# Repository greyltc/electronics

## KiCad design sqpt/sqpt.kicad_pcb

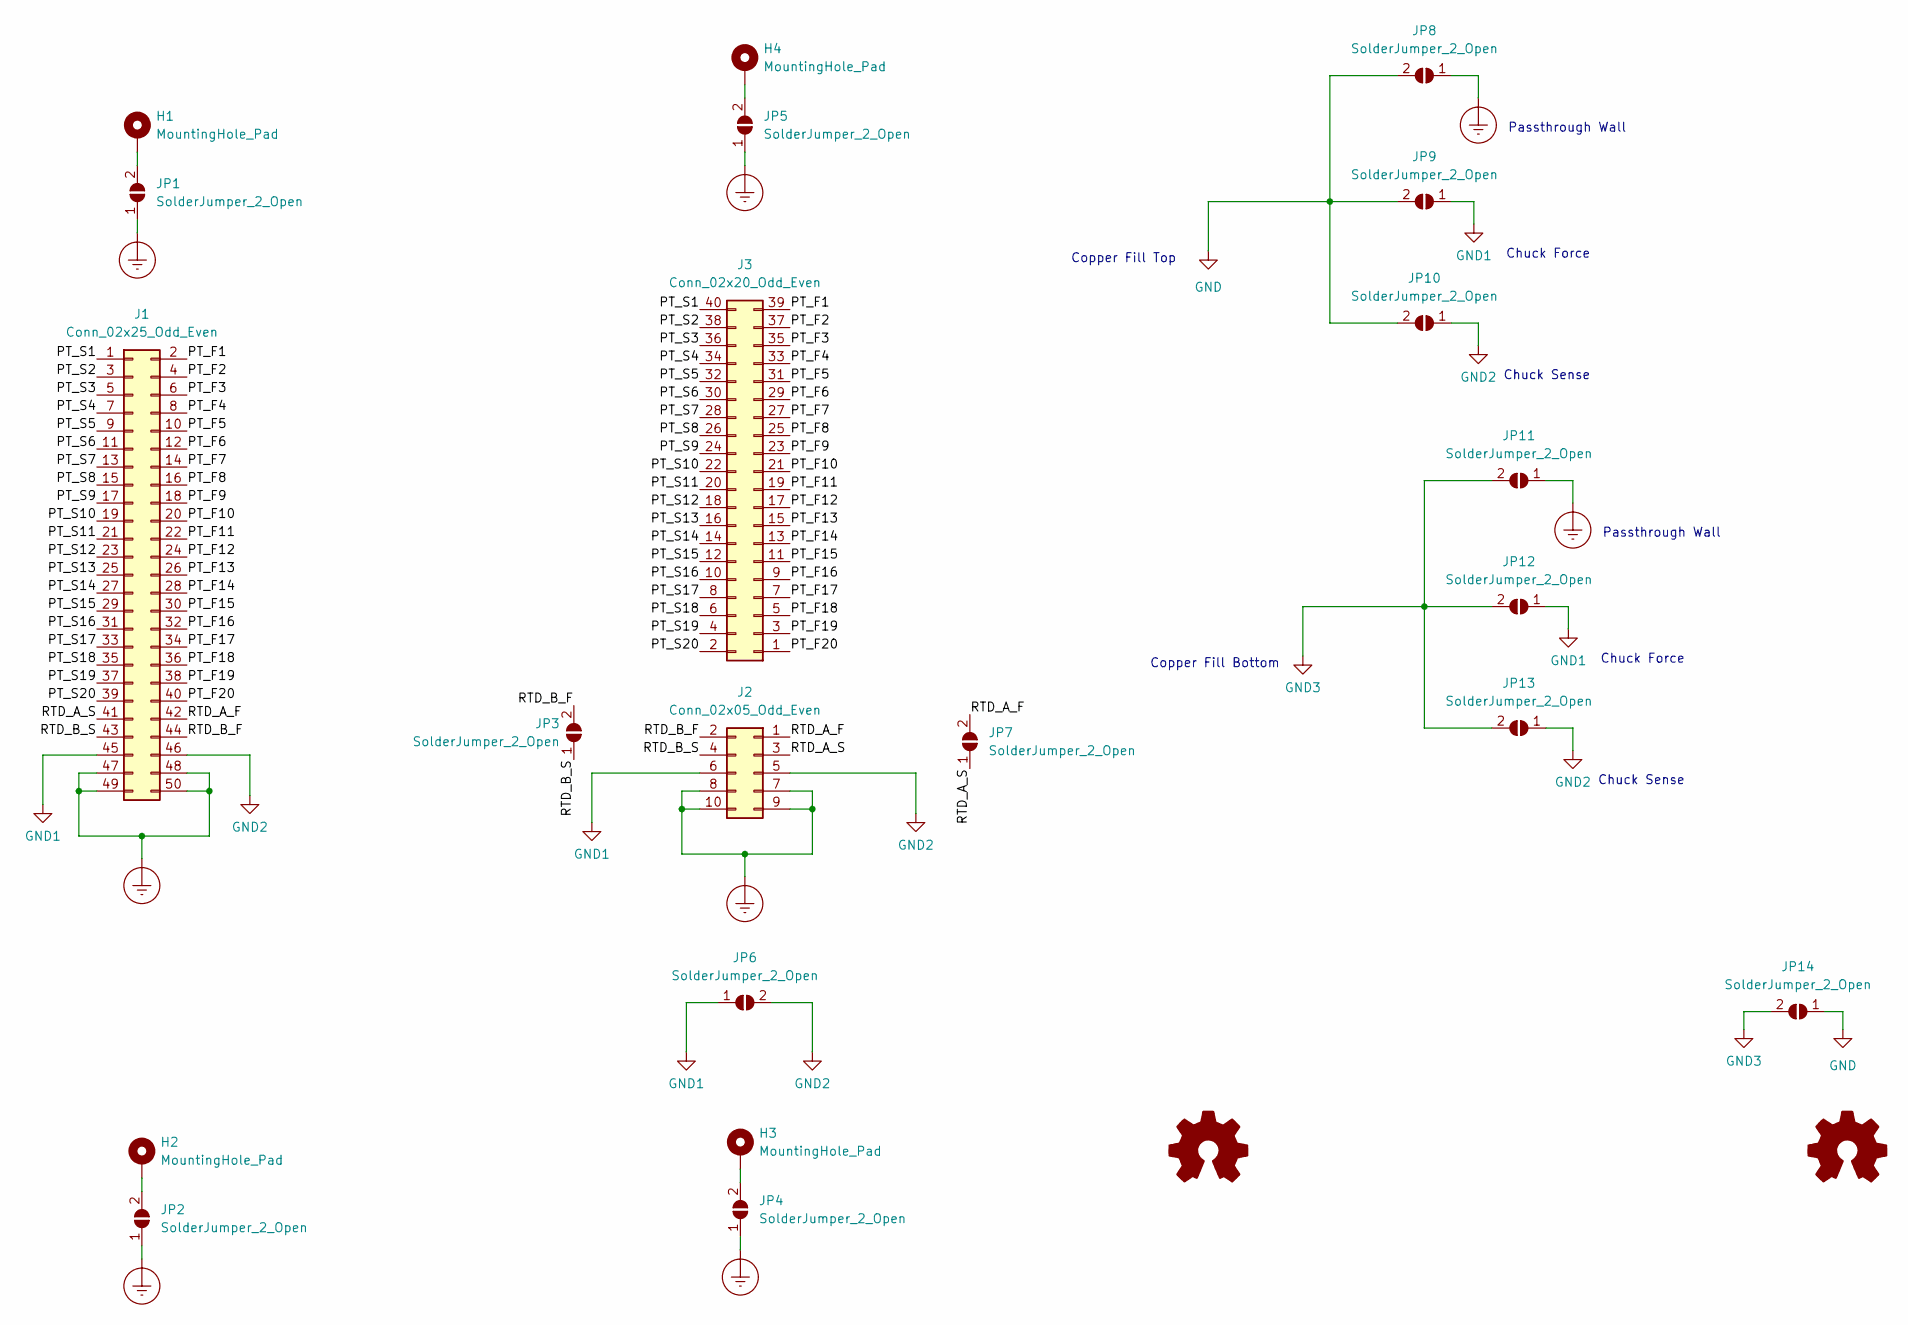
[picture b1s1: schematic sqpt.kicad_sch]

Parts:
H1, H2, H3, H4: MountingHole_Pad; MountingHole_3.2mm_M3_ISO14580_Pad
J1: Conn_02x25_Odd_Even; TST-125-01-G-D
J2: Conn_02x05_Odd_Even; PinHeader_2x05_P2.54mm_Vertical
J3: Conn_02x20_Odd_Even; TST-120-01-G-D
JP1, JP2, JP3, JP4, JP5, JP6, JP7, JP8, JP9, JP10, JP11, JP12, JP13, JP14: SolderJumper_2_Open; SolderJumper-2_P1.3mm_Open_RoundedPad1.0x1.5mm
LOGO1, LOGO2: Logo_Open_Hardware_Small; site_small

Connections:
/PT_F1: J1.2, J3.39
/PT_F2: J1.4, J3.37
/PT_F3: J1.6, J3.35
/PT_F4: J1.8, J3.33
/PT_F5: J1.10, J3.31
/PT_F6: J1.12, J3.29
/PT_F7: J1.14, J3.27
/PT_F8: J1.16, J3.25
/PT_F9: J1.18, J3.23
/PT_F10: J1.20, J3.21
/PT_F11: J1.22, J3.19
/PT_F12: J1.24, J3.17
/PT_F13: J1.26, J3.15
/PT_F14: J1.28, J3.13
/PT_F15: J1.30, J3.11
/PT_F16: J1.32, J3.9
/PT_F17: J1.34, J3.7
/PT_F18: J1.36, J3.5
/PT_F19: J1.38, J3.3
/PT_F20: J1.40, J3.1
/PT_S1: J1.1, J3.40
/PT_S2: J1.3, J3.38
/PT_S3: J1.5, J3.36
/PT_S4: J1.7, J3.34
/PT_S5: J1.9, J3.32
/PT_S6: J1.11, J3.30
/PT_S7: J1.13, J3.28
/PT_S8: J1.15, J3.26
/PT_S9: J1.17, J3.24
/PT_S10: J1.19, J3.22
/PT_S11: J1.21, J3.20
/PT_S12: J1.23, J3.18
/PT_S13: J1.25, J3.16
/PT_S14: J1.27, J3.14
/PT_S15: J1.29, J3.12
/PT_S16: J1.31, J3.10
/PT_S17: J1.33, J3.8
/PT_S18: J1.35, J3.6
/PT_S19: J1.37, J3.4
/PT_S20: J1.39, J3.2
/RTD_A_F: J1.42, J2.1, JP7.2 (B)
/RTD_A_S: J1.41, J2.3, JP7.1 (A)
/RTD_B_F: J1.44, J2.2, JP3.2 (B)
/RTD_B_S: J1.43, J2.4, JP3.1 (A)
Earth_Protective: J1.47, J1.48, J1.49, J1.50, J2.7, J2.8, J2.9, J2.10, JP1.1 (A), JP2.1 (A), JP4.1 (A), JP5.1 (A), JP8.1 (A), JP11.1 (A)
GND: JP8.2 (B), JP9.2 (B), JP10.2 (B), JP14.1 (A)
GND1: J1.45, J2.6, JP6.1 (A), JP9.1 (A), JP12.1 (A)
GND2: J1.46, J2.5, JP6.2 (B), JP10.1 (A), JP13.1 (A)
GND3: JP11.2 (B), JP12.2 (B), JP13.2 (B), JP14.2 (B)
unnamed: H1.1, JP1.2 (B)
unnamed: H2.1, JP2.2 (B)
unnamed: H3.1, JP4.2 (B)
unnamed: H4.1, JP5.2 (B)

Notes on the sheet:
Chuck Force
Passthrough Wall
Copper Fill Bottom
Chuck Sense
Copper Fill Top

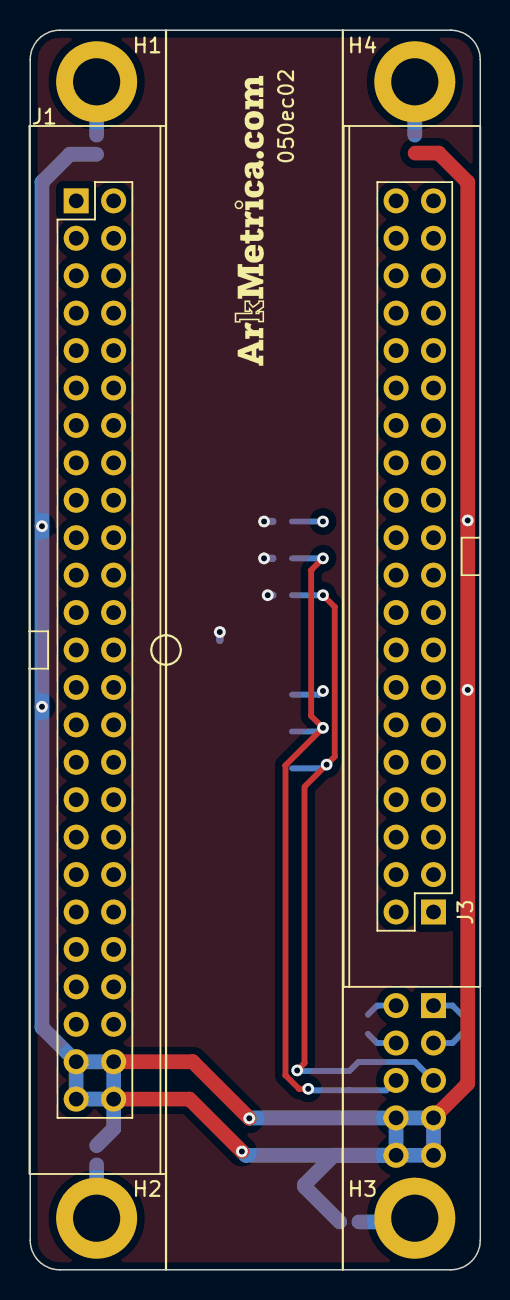
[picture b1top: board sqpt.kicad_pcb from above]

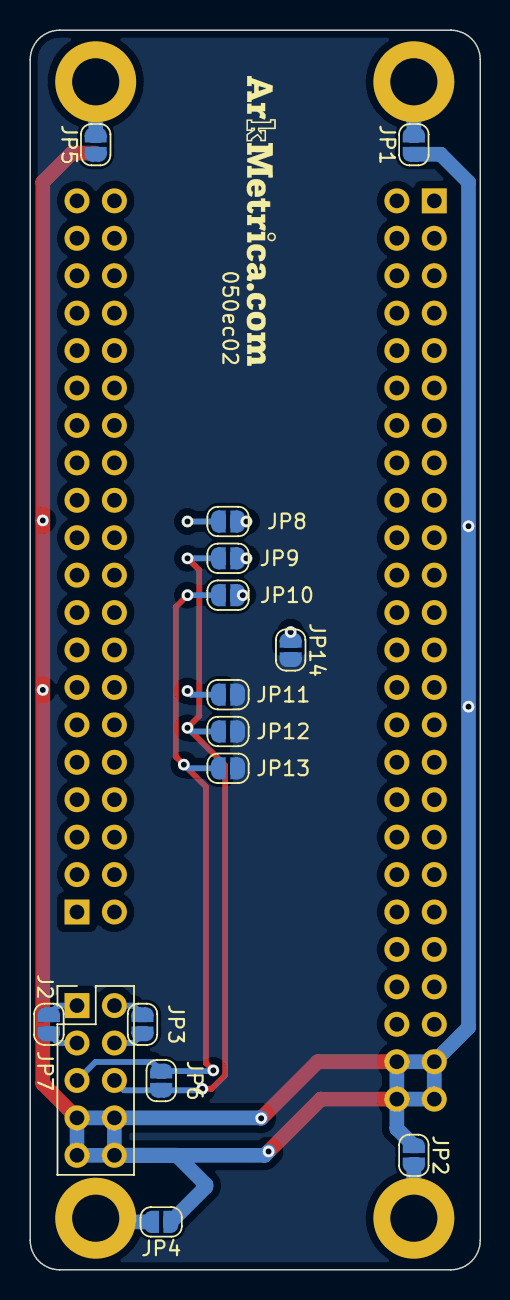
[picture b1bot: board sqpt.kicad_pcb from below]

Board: 4 copper layers, 30.5 x 84.1 mm, 23 parts (16 on the bottom side), 53 nets.

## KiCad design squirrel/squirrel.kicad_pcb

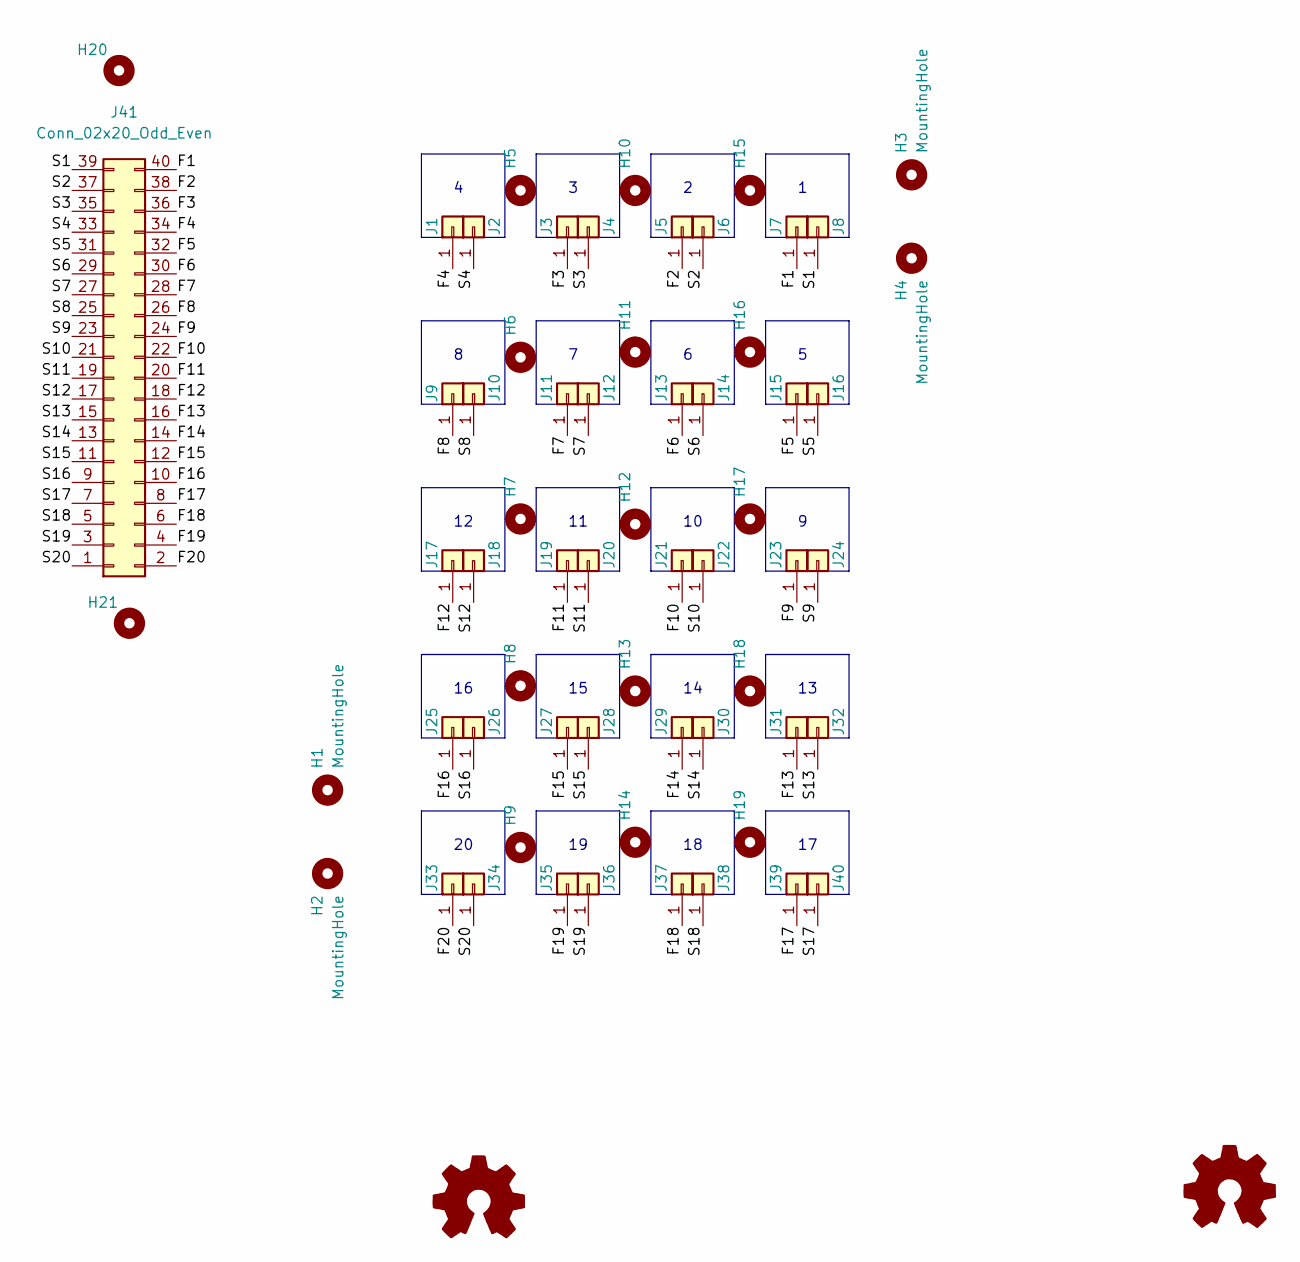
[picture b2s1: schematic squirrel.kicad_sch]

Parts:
H1, H4: MountingHole; MountingHole_6.4mm_M6
H2, H3: MountingHole; MountingHole_3.2mm_M3
H5, H6, H7, H8, H9, H10, H11, H12, H13, H14, H15, H16, H17, H18, H19, H20, H21: MountingHole; MountingHole_3.2mm_M3_wscrew
J1, J2, J3, J4, J5, J6, J7, J8, J9, J10, J11, J12, J13, J14, J15, J16, J17, J18, J19, J20, J21, J22, J23, J24, J25, J26, J27, J28, J29, J30, J31, J32, J33, J34, J35, J36, J37, J38, J39, J40: Conn_01x01; 0921
J41: Conn_02x20_Odd_Even; TST-120-01-G-D
LOGO1, LOGO2: Logo_Open_Hardware_Small; site_small

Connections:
/F1: J7.1, J41.40
/F2: J5.1, J41.38
/F3: J3.1, J41.36
/F4: J1.1, J41.34
/F5: J15.1, J41.32
/F6: J13.1, J41.30
/F7: J11.1, J41.28
/F8: J9.1, J41.26
/F9: J23.1, J41.24
/F10: J21.1, J41.22
/F11: J19.1, J41.20
/F12: J17.1, J41.18
/F13: J31.1, J41.16
/F14: J29.1, J41.14
/F15: J27.1, J41.12
/F16: J25.1, J41.10
/F17: J39.1, J41.8
/F18: J37.1, J41.6
/F19: J35.1, J41.4
/F20: J33.1, J41.2
/S1: J8.1, J41.39
/S2: J6.1, J41.37
/S3: J4.1, J41.35
/S4: J2.1, J41.33
/S5: J16.1, J41.31
/S6: J14.1, J41.29
/S7: J12.1, J41.27
/S8: J10.1, J41.25
/S9: J24.1, J41.23
/S10: J22.1, J41.21
/S11: J20.1, J41.19
/S12: J18.1, J41.17
/S13: J32.1, J41.15
/S14: J30.1, J41.13
/S15: J28.1, J41.11
/S16: J26.1, J41.9
/S17: J40.1, J41.7
/S18: J38.1, J41.5
/S19: J36.1, J41.3
/S20: J34.1, J41.1

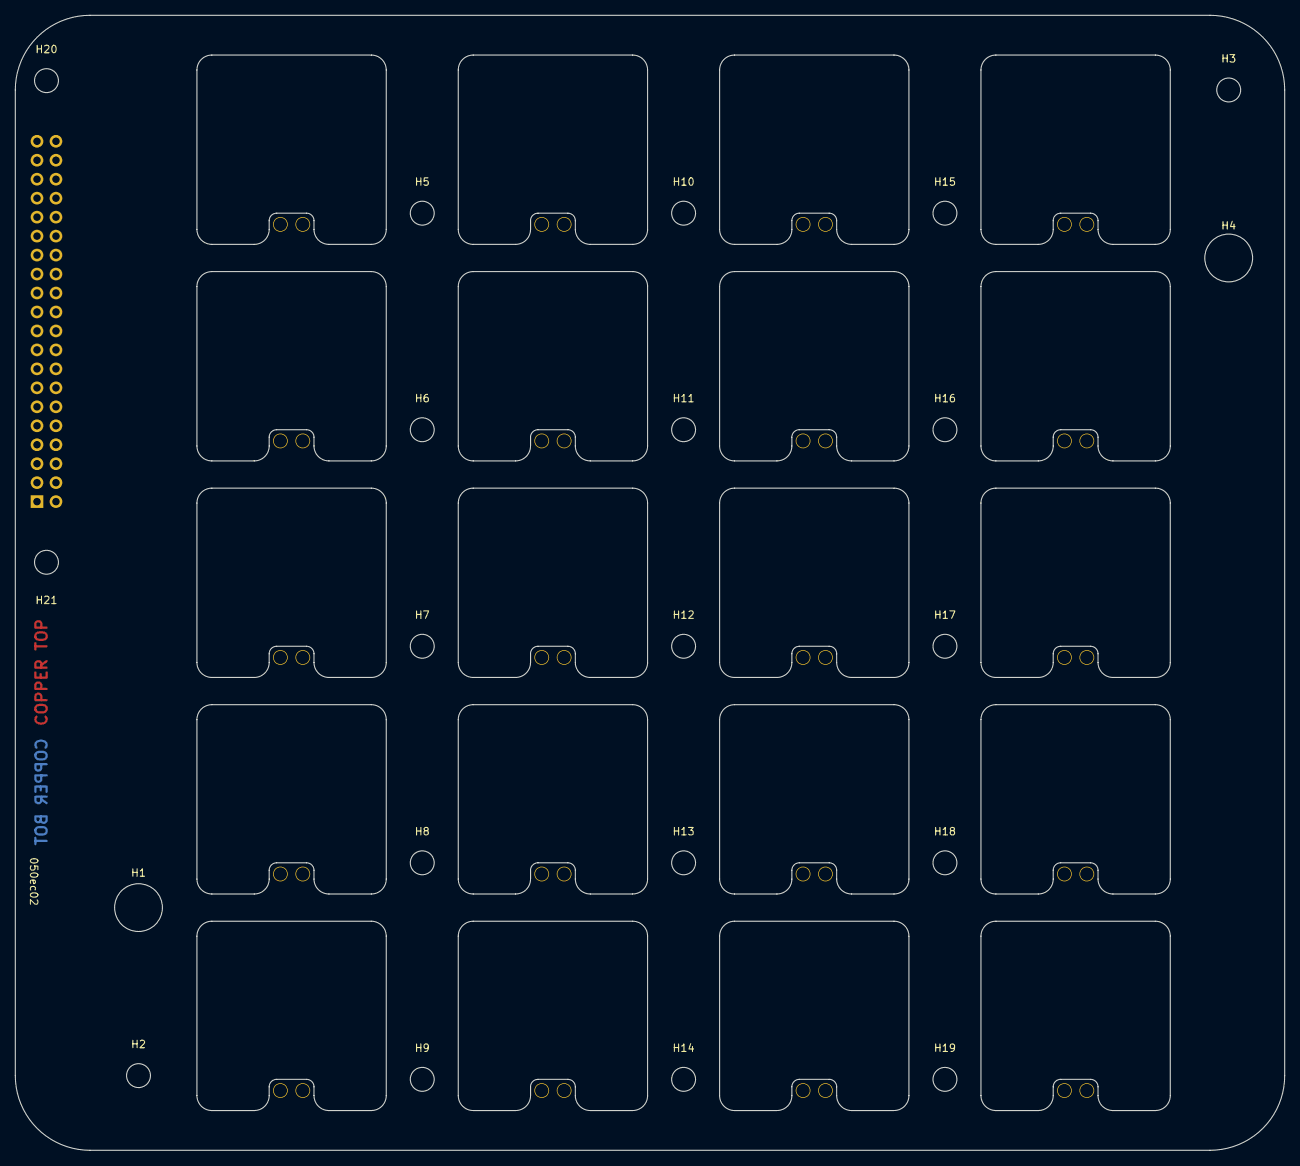
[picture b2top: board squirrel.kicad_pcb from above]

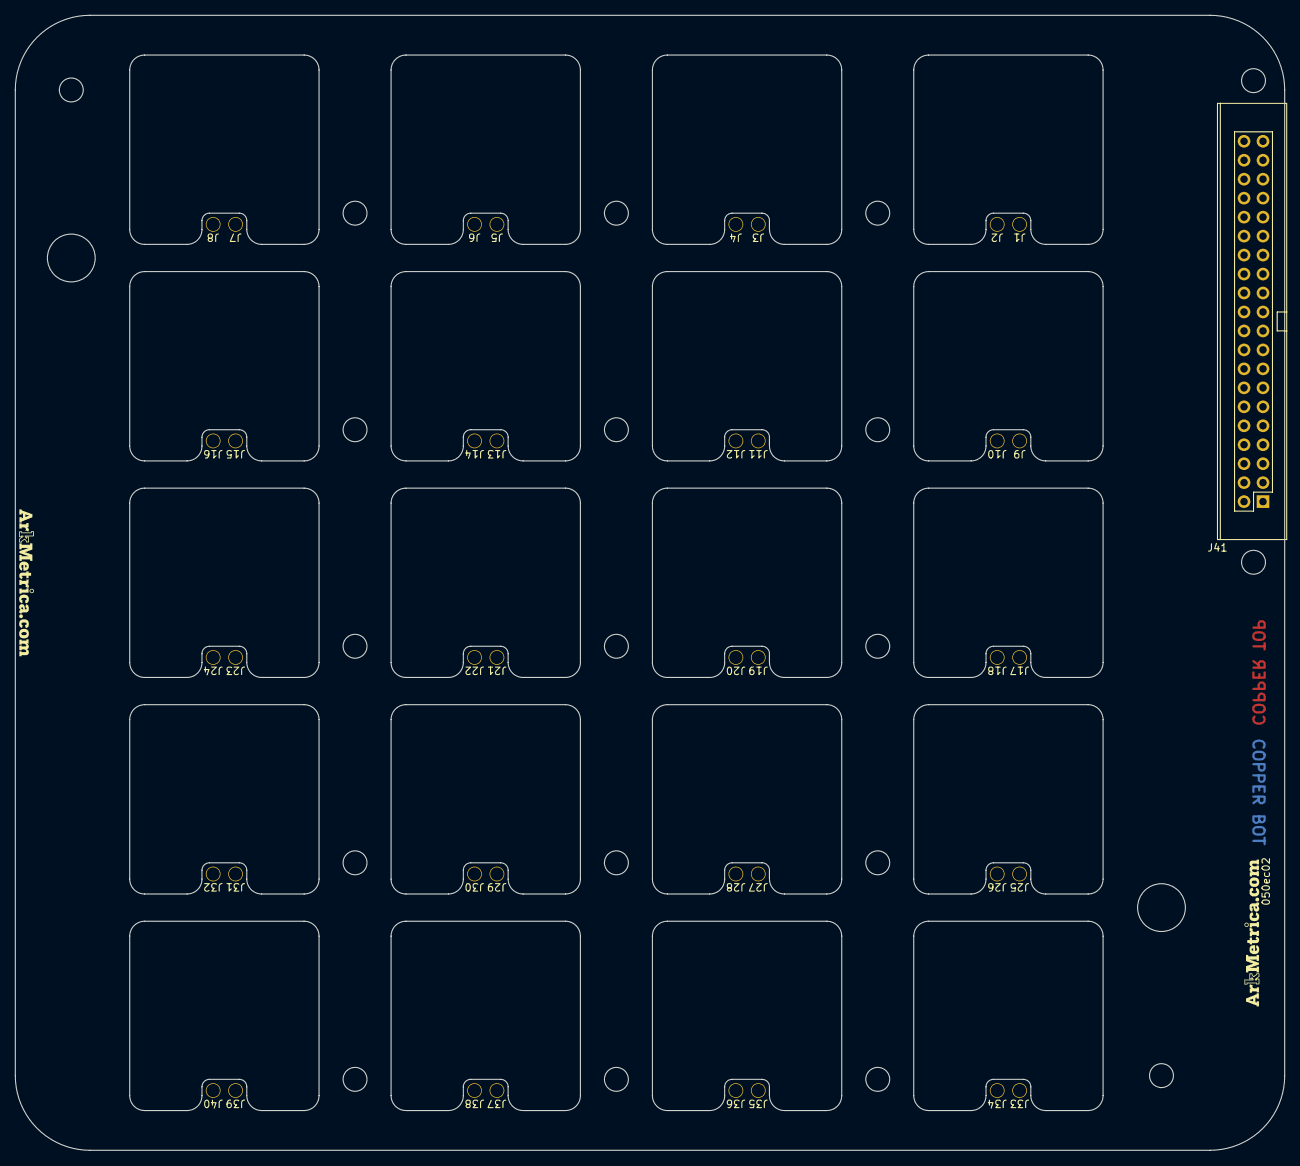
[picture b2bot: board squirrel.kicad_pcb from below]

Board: 4 copper layers, 170.0 x 152.0 mm, 64 parts (60 on the bottom side), 40 nets.

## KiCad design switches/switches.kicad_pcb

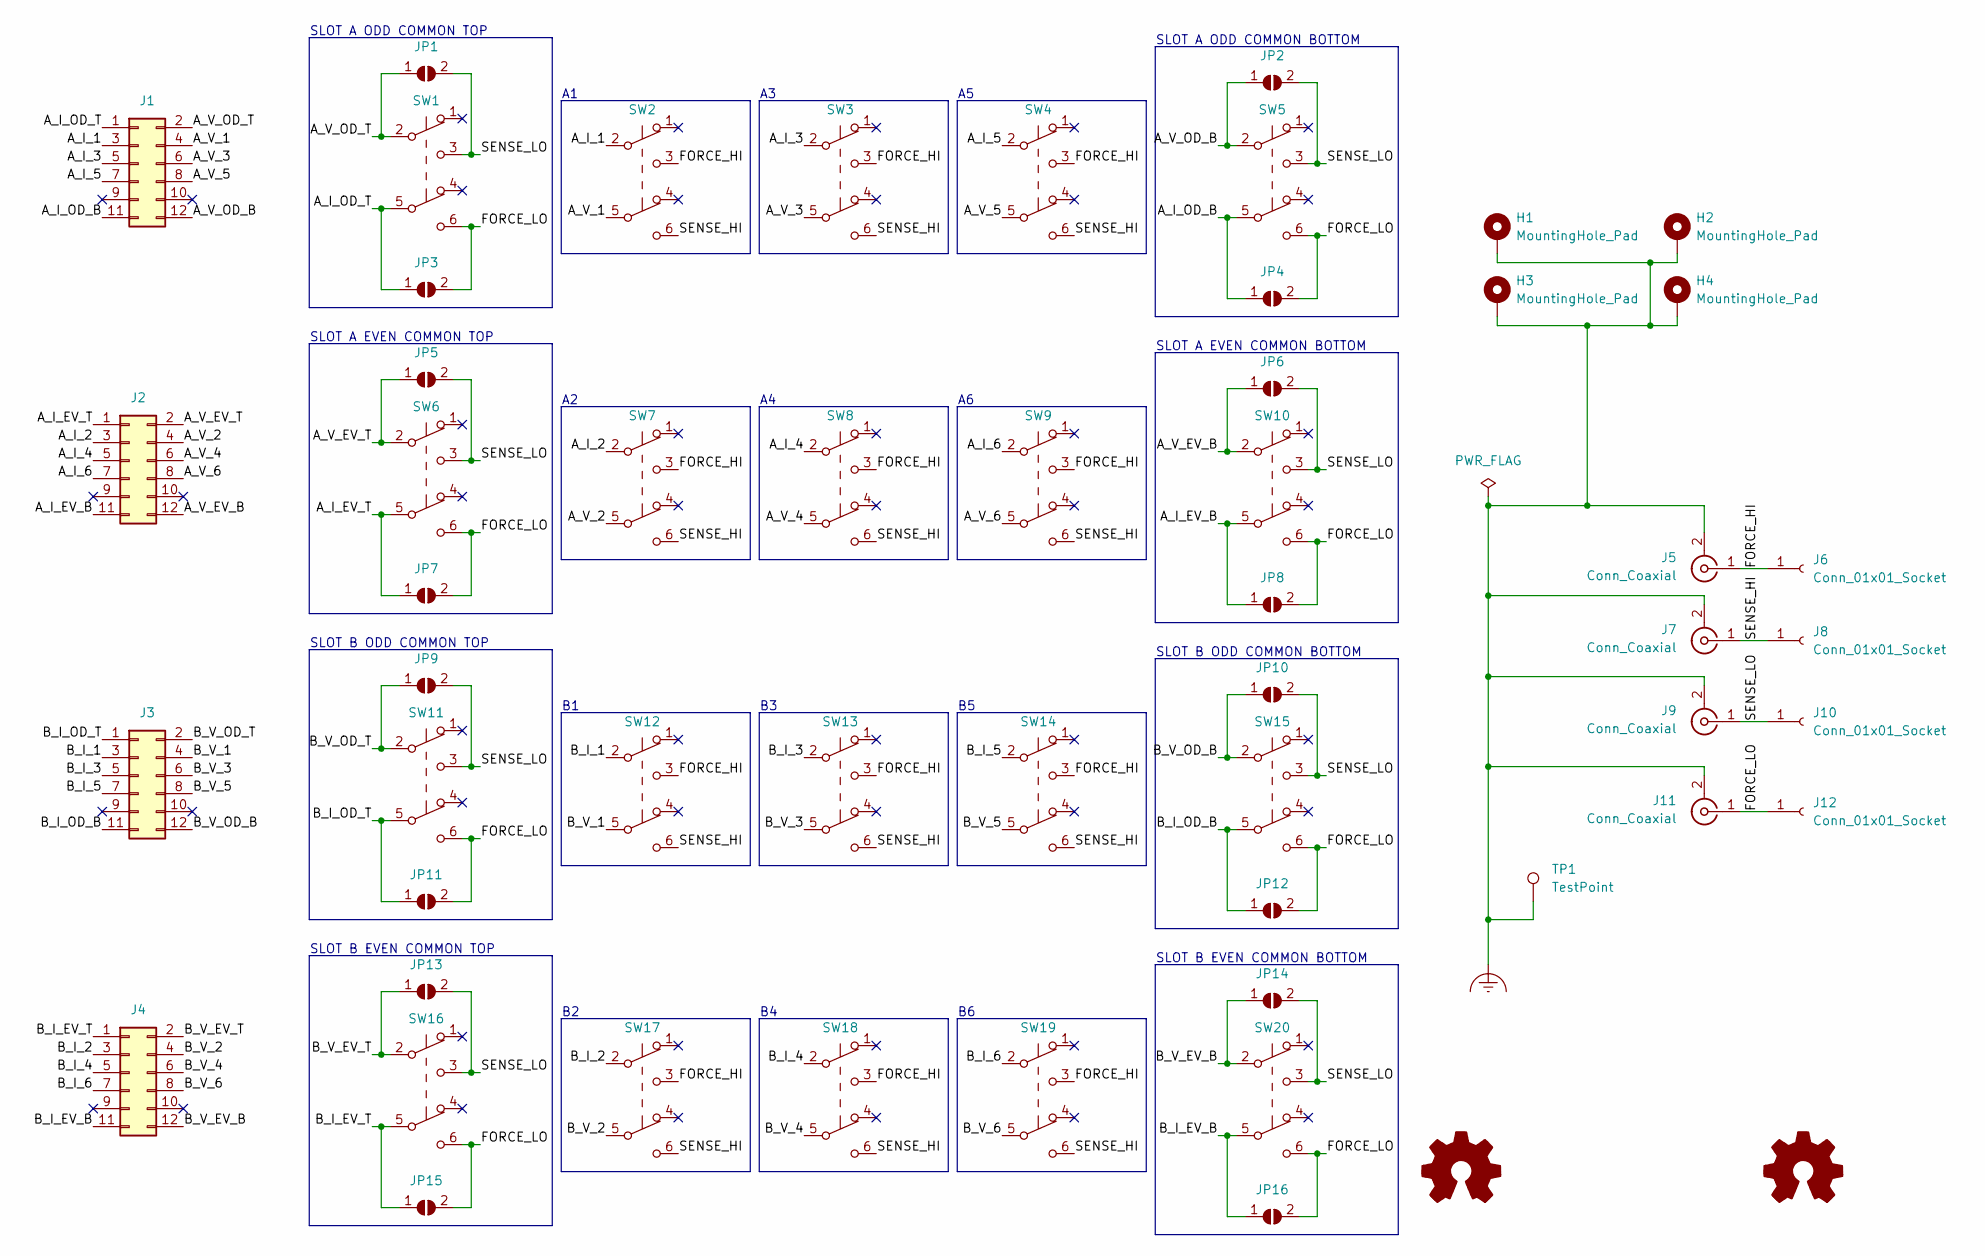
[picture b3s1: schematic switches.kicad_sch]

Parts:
H1, H2, H3, H4: MountingHole_Pad; MountingHole_3.2mm_M3_ISO7380_Pad
J1, J2, J3, J4: Conn_02x06_Odd_Even; IDC-Header_2x06_P2.54mm_Horizontal
J5, J7, J9, J11: Conn_Coaxial; BNC_TEConnectivity_1478035_Horizontal
J6, J8, J10, J12: Conn_01x01_Socket; Banana_Cliff_FCR7350x_S16N-PC_Horizontal
JP1, JP2, JP3, JP4, JP5, JP6, JP7, JP8, JP9, JP10, JP11, JP12, JP13, JP14, JP15, JP16: SolderJumper_2_Open; SolderJumper-2_P1.3mm_Open_TrianglePad1.0x1.5mm
SW1, SW2, SW3, SW4, SW5, SW6, SW7, SW8, SW9, SW10, SW11, SW12, SW13, SW14, SW15, SW16, SW17, SW18, SW19, SW20: SW_Push_DPDT; SW_CuK_JS202011CQN_DPDT_Straight; Part# JS202011CQN
SYM1, SYM2: Logo_Open_Hardware_Small; site_small
TP1: TestPoint; TestPoint_Bridge_Pitch2.54mm_Drill1.0mm

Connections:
/A_I_1: J1.3, SW2.2 (B)
/A_I_2: J2.3, SW7.2 (B)
/A_I_3: J1.5, SW3.2 (B)
/A_I_4: J2.5, SW8.2 (B)
/A_I_5: J1.7, SW4.2 (B)
/A_I_6: J2.7, SW9.2 (B)
/A_I_EV_B: J2.11, JP8.1 (A), SW10.5 (B)
/A_I_EV_T: J2.1, JP7.1 (A), SW6.5 (B)
/A_I_OD_B: J1.11, JP4.1 (A), SW5.5 (B)
/A_I_OD_T: J1.1, JP3.1 (A), SW1.5 (B)
/A_V_1: J1.4, SW2.5 (B)
/A_V_2: J2.4, SW7.5 (B)
/A_V_3: J1.6, SW3.5 (B)
/A_V_4: J2.6, SW8.5 (B)
/A_V_5: J1.8, SW4.5 (B)
/A_V_6: J2.8, SW9.5 (B)
/A_V_EV_B: J2.12, JP6.1 (A), SW10.2 (B)
/A_V_EV_T: J2.2, JP5.1 (A), SW6.2 (B)
/A_V_OD_B: J1.12, JP2.1 (A), SW5.2 (B)
/A_V_OD_T: J1.2, JP1.1 (A), SW1.2 (B)
/B_I_1: J3.3, SW12.2 (B)
/B_I_2: J4.3, SW17.2 (B)
/B_I_3: J3.5, SW13.2 (B)
/B_I_4: J4.5, SW18.2 (B)
/B_I_5: J3.7, SW14.2 (B)
/B_I_6: J4.7, SW19.2 (B)
/B_I_EV_B: J4.11, JP16.1 (A), SW20.5 (B)
/B_I_EV_T: J4.1, JP15.1 (A), SW16.5 (B)
/B_I_OD_B: J3.11, JP12.1 (A), SW15.5 (B)
/B_I_OD_T: J3.1, JP11.1 (A), SW11.5 (B)
/B_V_1: J3.4, SW12.5 (B)
/B_V_2: J4.4, SW17.5 (B)
/B_V_3: J3.6, SW13.5 (B)
/B_V_4: J4.6, SW18.5 (B)
/B_V_5: J3.8, SW14.5 (B)
/B_V_6: J4.8, SW19.5 (B)
/B_V_EV_B: J4.12, JP14.1 (A), SW20.2 (B)
/B_V_EV_T: J4.2, JP13.1 (A), SW16.2 (B)
/B_V_OD_B: J3.12, JP10.1 (A), SW15.2 (B)
/B_V_OD_T: J3.2, JP9.1 (A), SW11.2 (B)
/FORCE_HI: J5.1 (In), J6.1, SW2.3 (C), SW3.3 (C), SW4.3 (C), SW7.3 (C), SW8.3 (C), SW9.3 (C), SW12.3 (C), SW13.3 (C), SW14.3 (C), SW17.3 (C), SW18.3 (C), SW19.3 (C)
/FORCE_LO: J11.1 (In), J12.1, JP3.2 (B), JP4.2 (B), JP7.2 (B), JP8.2 (B), JP11.2 (B), JP12.2 (B), JP15.2 (B), JP16.2 (B), SW1.6 (C), SW5.6 (C), SW6.6 (C), SW10.6 (C), SW11.6 (C), SW15.6 (C), SW16.6 (C), SW20.6 (C)
/SENSE_HI: J7.1 (In), J8.1, SW2.6 (C), SW3.6 (C), SW4.6 (C), SW7.6 (C), SW8.6 (C), SW9.6 (C), SW12.6 (C), SW13.6 (C), SW14.6 (C), SW17.6 (C), SW18.6 (C), SW19.6 (C)
/SENSE_LO: J9.1 (In), J10.1, JP1.2 (B), JP2.2 (B), JP5.2 (B), JP6.2 (B), JP9.2 (B), JP10.2 (B), JP13.2 (B), JP14.2 (B), SW1.3 (C), SW5.3 (C), SW6.3 (C), SW10.3 (C), SW11.3 (C), SW15.3 (C), SW16.3 (C), SW20.3 (C)
Earth_Clean: H1.1, H2.1, H3.1, H4.1, J5.2 (Ext), J7.2 (Ext), J9.2 (Ext), J11.2 (Ext), TP1.1

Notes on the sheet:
SLOT B ODD COMMON BOTTOM
SLOT B ODD COMMON TOP
SLOT A EVEN COMMON TOP
SLOT A ODD COMMON BOTTOM
SLOT B EVEN COMMON TOP
SLOT B EVEN COMMON BOTTOM
SLOT A EVEN COMMON BOTTOM
SLOT A ODD COMMON TOP

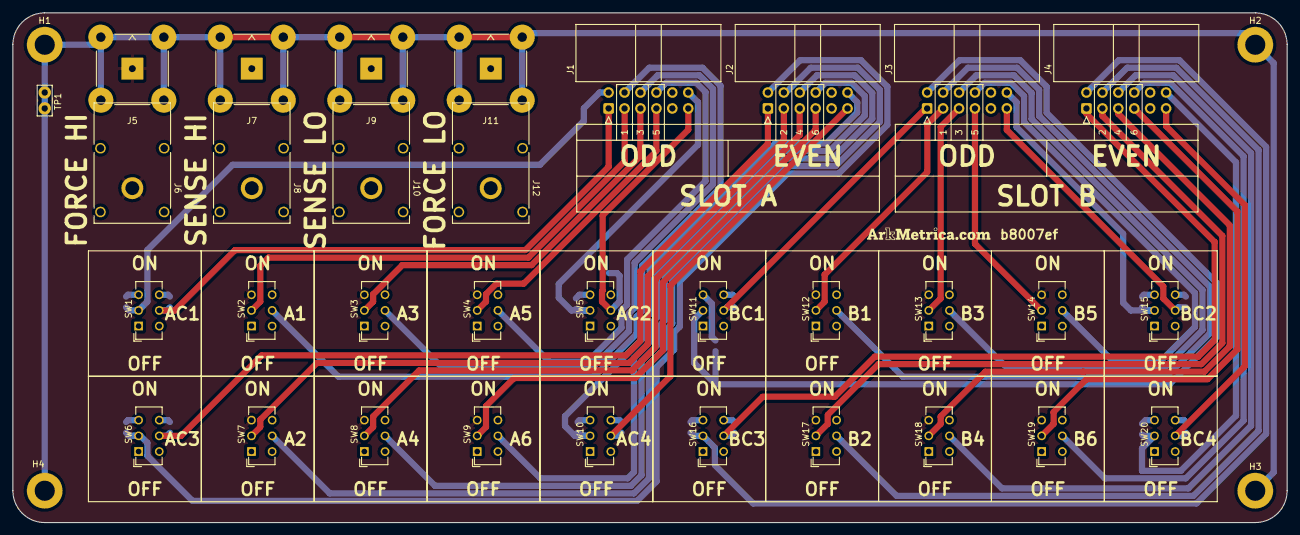
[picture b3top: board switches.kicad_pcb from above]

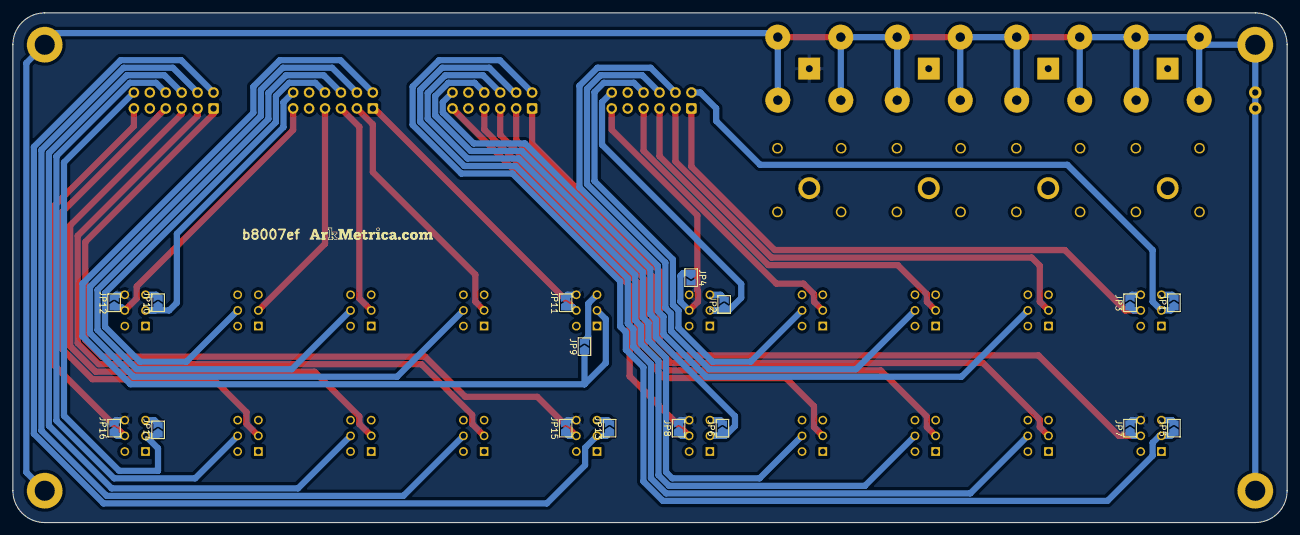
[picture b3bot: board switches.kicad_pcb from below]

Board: 4 copper layers, 203.2 x 81.3 mm, 55 parts (17 on the bottom side), 45 nets.

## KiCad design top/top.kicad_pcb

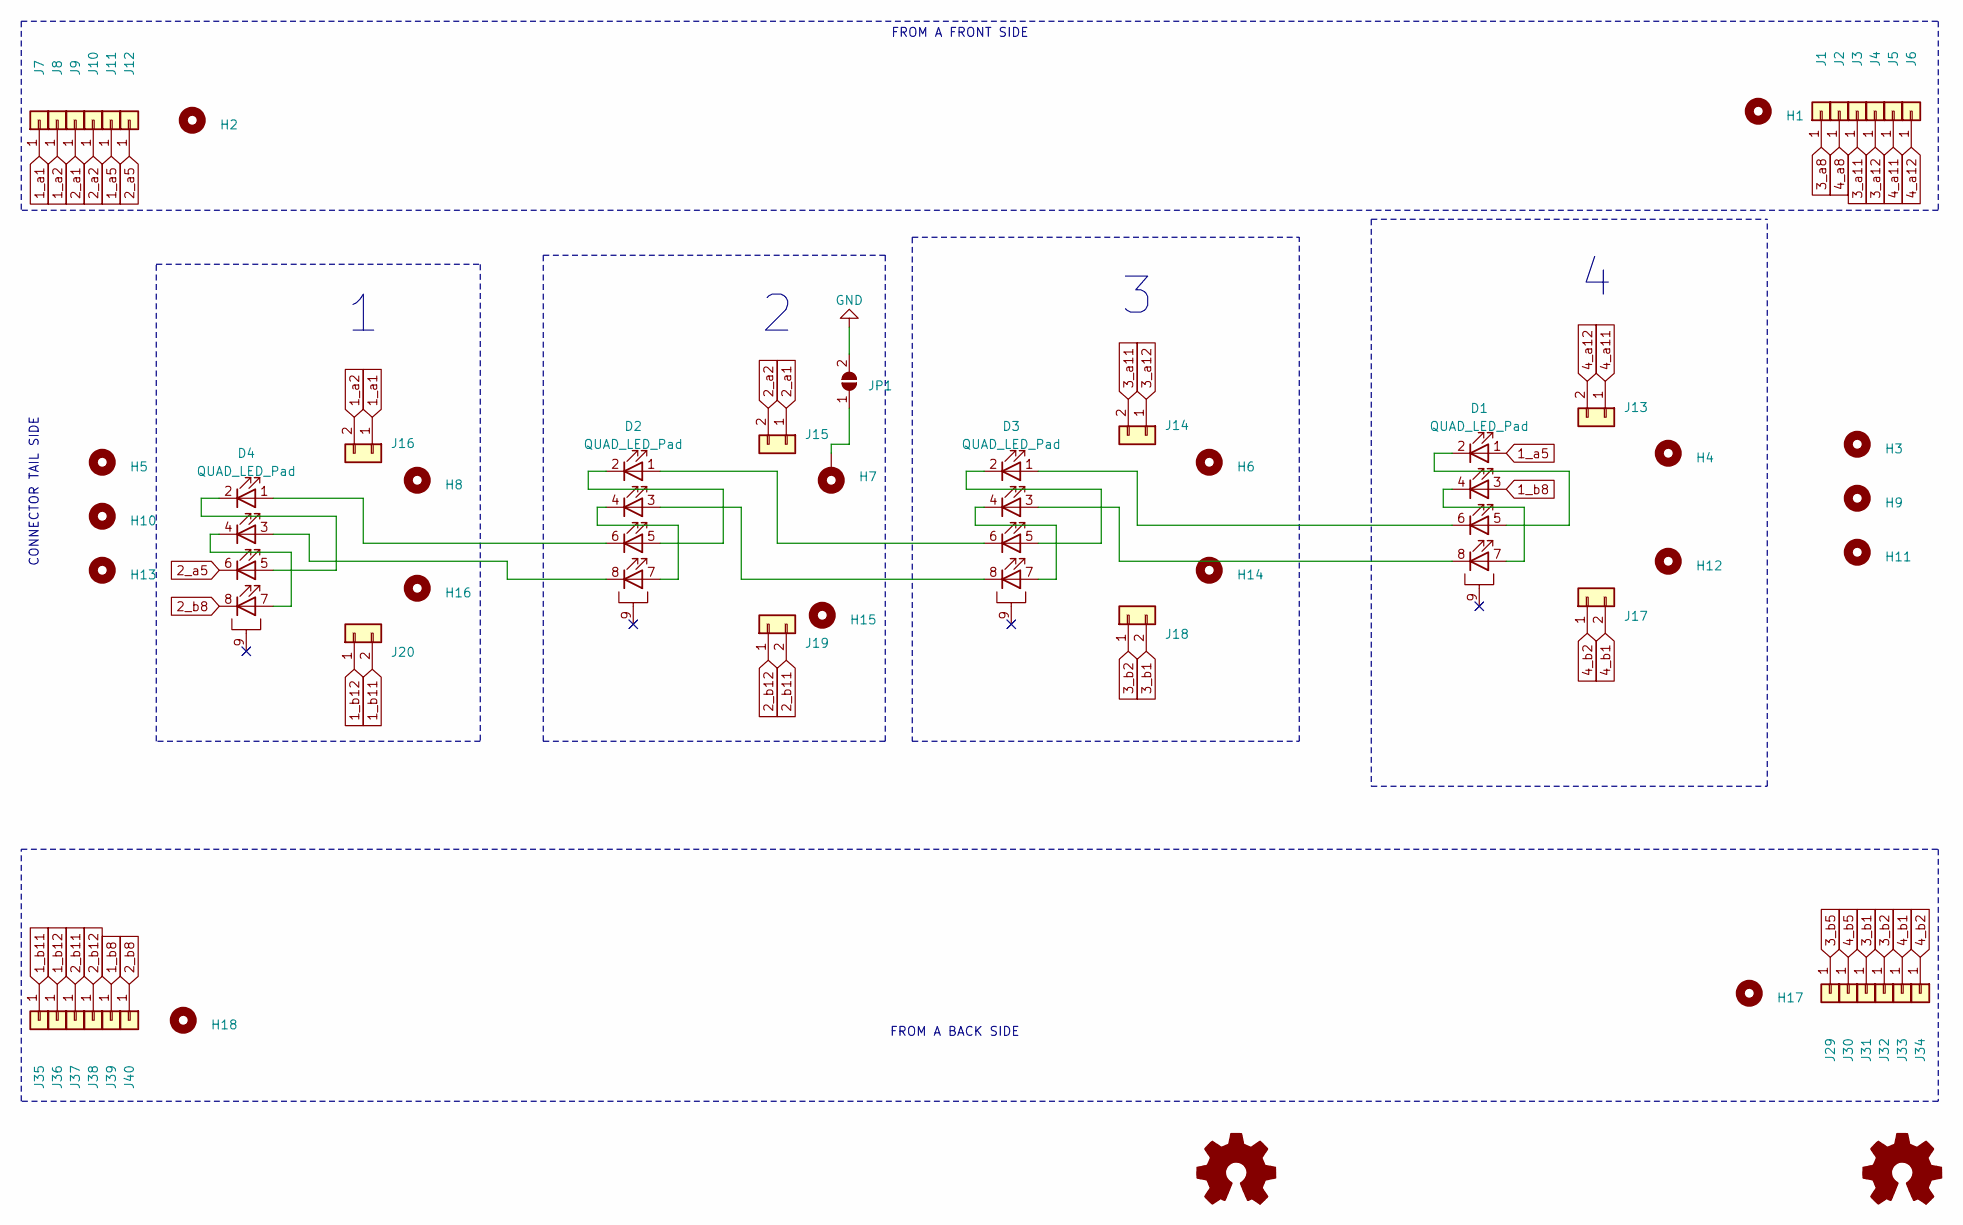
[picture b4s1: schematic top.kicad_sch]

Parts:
D1, D2, D3, D4: QUAD_LED_Pad; luxigen_8.02X8.02_FR4
H1, H2, H4, H6, H8, H12, H14, H15, H16, H17, H18: MountingHole; MountingHole_2.2mm_M2
H3, H5, H11, H13: MountingHole; MountingHole_3.2mm_M3
H7: MountingHole_Pad; MountingHole_2.2mm_M2_DIN965_Pad
H9, H10: MountingHole; MountingHole_5.5mm
J1, J2, J3, J4, J5, J6, J7, J8, J9, J10, J11, J12, J29, J30, J31, J32, J33, J34, J35, J36, J37, J38, J39, J40: Conn_01x01; 5342
J13, J14, J15, J16, J17, J18, J19, J20: Conn_01x02; MILLMAX_816-22-002-10-007101
JP1: SolderJumper_2_Open; SolderJumper-2_P1.3mm_Open_RoundedPad1.0x1.5mm
LOGO1, LOGO2: Logo_Open_Hardware_Small; logo_small

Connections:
1_a1: J7.1, J16.1
1_a2: J8.1, J16.2
1_a5: D1.1 (IR_A_ANODE), J11.1
1_b8: D1.3 (CW_B_ANODE), J39.1
1_b11: J20.2, J35.1
1_b12: J20.1, J36.1
2_a1: J9.1, J15.1
2_a2: J10.1, J15.2
2_a5: D4.6 (IR_C_CATHODE), J12.1
2_b8: D4.8 (CW_D_CATHODE), J40.1
2_b11: J19.2, J37.1
2_b12: J19.1, J38.1
3_a8: J1.1
3_a11: J3.1, J14.2
3_a12: J4.1, J14.1
3_b1: J18.2, J31.1
3_b2: J18.1, J32.1
3_b5: J29.1
4_a8: J2.1
4_a11: J5.1, J13.1
4_a12: J6.1, J13.2
4_b1: J17.2, J33.1
4_b2: J17.1, J34.1
4_b5: J30.1
GND: JP1.2 (B)
unnamed: D1.2 (IR_A_CATHODE), D1.5 (IR_C_ANODE)
unnamed: D1.4 (CW_B_CATHODE), D1.7 (CW_D_ANODE)
unnamed: D1.6 (IR_C_CATHODE), D3.1 (IR_A_ANODE)
unnamed: D1.8 (CW_D_CATHODE), D3.3 (CW_B_ANODE)
unnamed: D2.1 (IR_A_ANODE), D3.6 (IR_C_CATHODE)
unnamed: D2.2 (IR_A_CATHODE), D2.5 (IR_C_ANODE)
unnamed: D2.3 (CW_B_ANODE), D3.8 (CW_D_CATHODE)
unnamed: D2.4 (CW_B_CATHODE), D2.7 (CW_D_ANODE)
unnamed: D2.6 (IR_C_CATHODE), D4.1 (IR_A_ANODE)
unnamed: D2.8 (CW_D_CATHODE), D4.3 (CW_B_ANODE)
unnamed: D3.2 (IR_A_CATHODE), D3.5 (IR_C_ANODE)
unnamed: D3.4 (CW_B_CATHODE), D3.7 (CW_D_ANODE)
unnamed: D4.2 (IR_A_CATHODE), D4.5 (IR_C_ANODE)
unnamed: D4.4 (CW_B_CATHODE), D4.7 (CW_D_ANODE)
unnamed: H7.1, JP1.1 (A)

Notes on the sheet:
CONNECTOR TAIL SIDE
FROM A BACK SIDE
FROM A FRONT SIDE

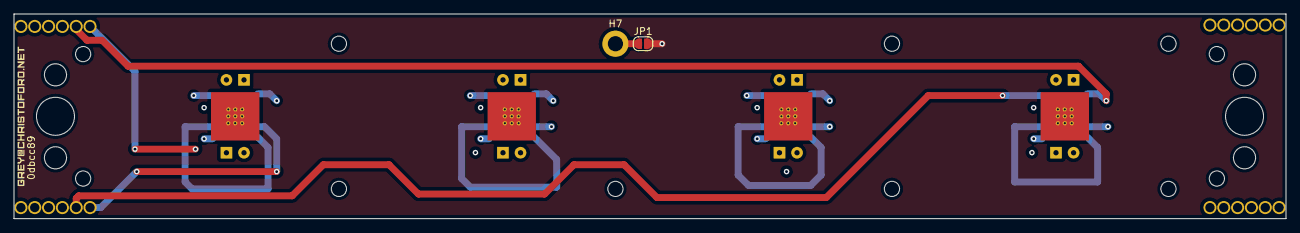
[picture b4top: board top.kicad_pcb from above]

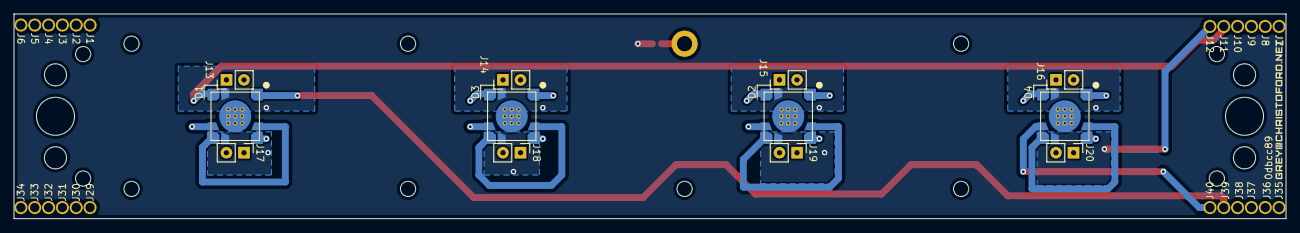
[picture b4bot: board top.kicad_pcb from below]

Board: 4 copper layers, 184.0 x 29.6 mm, 57 parts (37 on the bottom side), 35 nets.

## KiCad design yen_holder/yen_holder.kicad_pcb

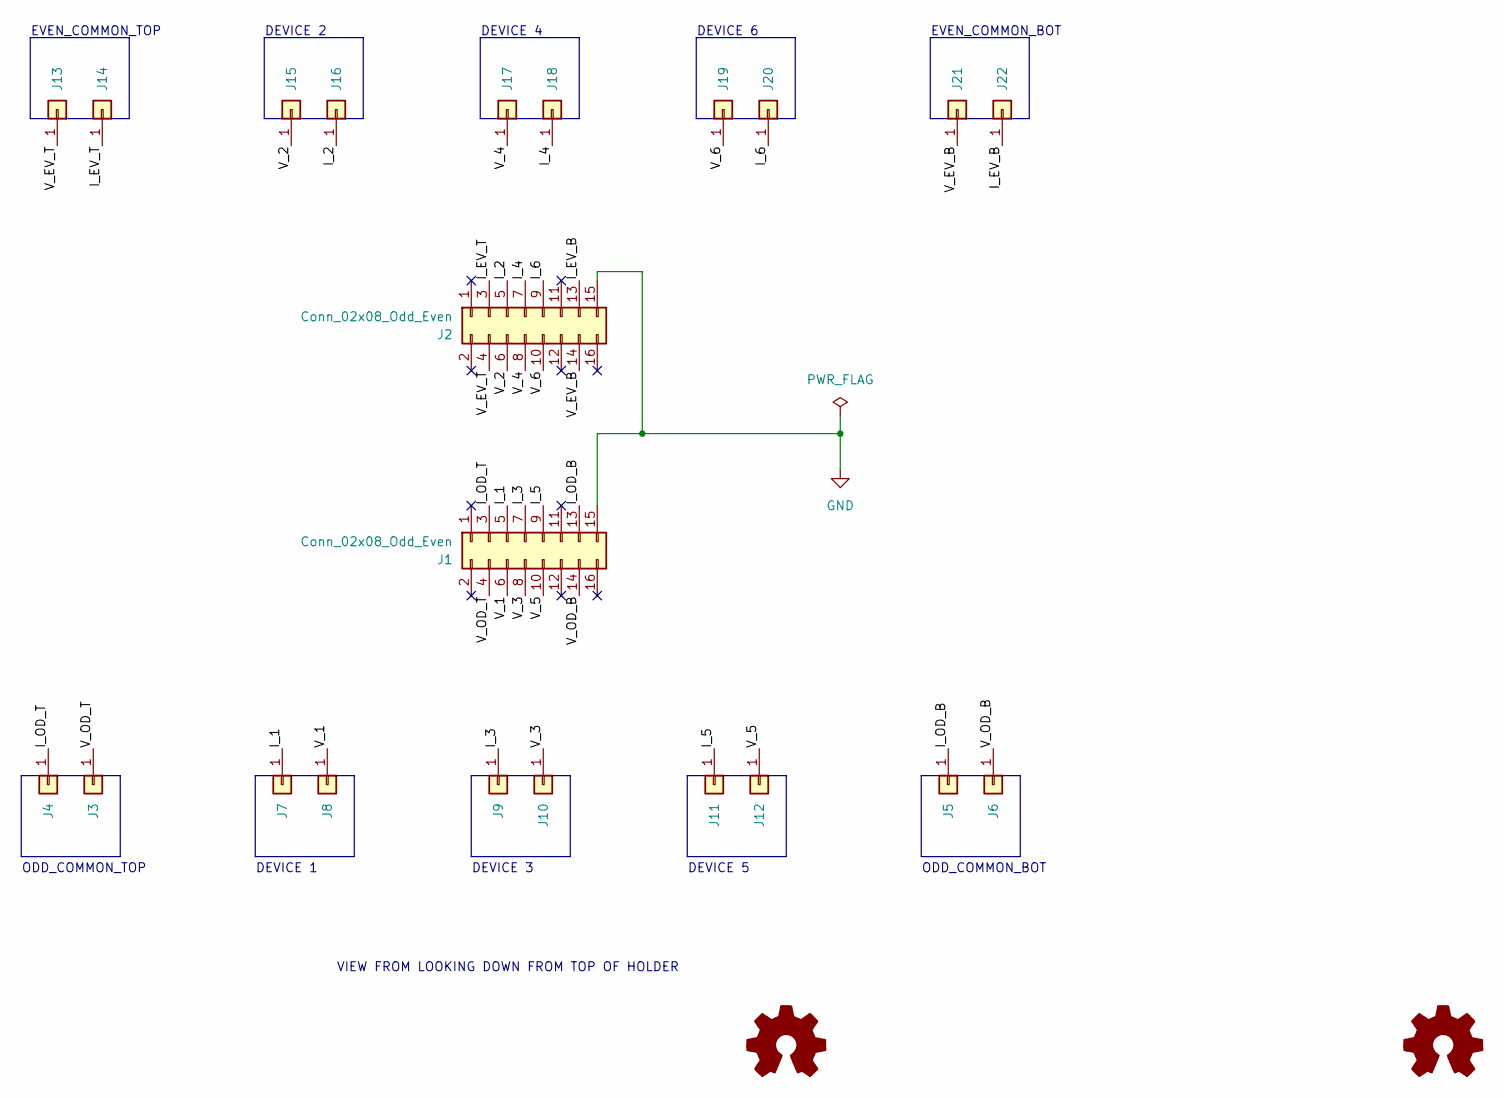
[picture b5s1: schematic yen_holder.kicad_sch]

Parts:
J1: Conn_02x08_Odd_Even; HIF3FC-16PA-2.54DSA(71); partno_receptical HIF3FB-16DA-2.54DSA(71)
J2: Conn_02x08_Odd_Even; HIF3FC-16PA-2.54DSA(71); partno_header HIF3FC -16PA-2.54DSA(71)
J3, J4, J5, J6, J7, J8, J9, J10, J11, J12, J13, J14, J15, J16, J17, J18, J19, J20, J21, J22: Conn_01x01; S25-022+P25-4023_OFF
SYM1, SYM2: Logo_Open_Hardware_Small; logo_small

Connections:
/I_1: J1.5, J7.1
/I_2: J2.5, J16.1
/I_3: J1.7, J9.1
/I_4: J2.7, J18.1
/I_5: J1.9, J11.1
/I_6: J2.9, J20.1
/I_EV_B: J2.13, J22.1
/I_EV_T: J2.3, J14.1
/I_OD_B: J1.13, J5.1
/I_OD_T: J1.3, J4.1
/V_1: J1.6, J8.1
/V_2: J2.6, J15.1
/V_3: J1.8, J10.1
/V_4: J2.8, J17.1
/V_5: J1.10, J12.1
/V_6: J2.10, J19.1
/V_EV_B: J2.14, J21.1
/V_EV_T: J2.4, J13.1
/V_OD_B: J1.14, J6.1
/V_OD_T: J1.4, J3.1
GND: J1.15, J2.15

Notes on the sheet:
ODD_COMMON_TOP
EVEN_COMMON_BOT
DEVICE 6
DEVICE 4
ODD_COMMON_BOT
VIEW FROM LOOKING DOWN FROM TOP OF HOLDER
DEVICE 3
DEVICE 5
DEVICE 2
EVEN_COMMON_TOP
DEVICE 1
